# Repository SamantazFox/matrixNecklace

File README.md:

# matrixNecklace

Index
-----

* [Introduction](#introduction)
* [Project's Description](#projects-description)
* [Folders](#folders)
* [Known Issues](#known-issues)
* [To Do](#to-do)

Introduction
------------

This project is a simple customizable necklace, based on an AtTiny2313a (or
alternatively an ATtiny48/88) and a 8x8 dot LED matrix.

The very first idea came from furrtek's mind, called **jewelmatrix**. You can
find his project on [his website](http://furrtek.free.fr/?a=jewelmatrix)
(french).

The idea behind this project was to improve Furrtek's project and add a few
options, such as a rechargeable Li-Ion battery (instead of a coin cell) and a
cross-platform tool to add custom patterns on the fly, without the need to
rebuild and flash the ATtiny every time.

Implemented features :
	* Fully customizable patterns
	* Rechargeable by USB

Planned features :
    * Easy on-the-fly programmation by any device running **\*nix**,
    **windows**, **MacOS** or **android** operating system, using the device's
    screen as the transmission support
    * USB connection to host device (faster than screen transmision)

Project's Description
-------------------

* matrixEditor
    - matrixEditor is the UI for matrixNecklace's patterns creation.
    - Based on the FLTK graphic library.
    - Still at experimental level.

* matrixNecklace
    - One of the following microntrollers:
        * An ATtiny2313/2313a/4313: easy soldering solution
        * An ATtiny48/88: if you feel adventurous to solder QFN32 :P
    - 8x8 dot LED matrix
    - Li-Ion battery, which can be recharged via micro USB type B

Folders
-------

* **/doc**
    - Sphinx documentation
    - Datasheets

* **/editor**
    - C++ Cross-platform editor source code
    - Compile script and instructions

* **/firmware**
    - AVR hardware source code
    - Compile script and instructions
    - Basic patterns (for reference)
    - Arduino sketch used to determine matrixes' pinout

* **/hardware**
    - **/hardware/schematic**
        - KiCad librarties
        - KiCad schematic/pcb files
        - Bill of material

* **/licenses**
    - Project's license file(s)
    - Every libraries used's specific license file(s)

Known Issues
------------

* 50/60 Hz differences may cause problems for screen transmission upload

To Do
-----

* Documentation
    - Sphinx documentation
    - Compiling HowTo

* Editor
    - Patterns import/export
    - Patterns ordering and timings
    - Integrated compiler (and it's output)
    - Device uploader

* Firmware
    - Correct pinout/registers match
    - Update for AtTiny48/88
    - Create custom bootloader
    - Add USB support

* Hardware
    - Finish pinout
    - Finish chips libraries
    - Release schematics
    - Create BOM
    - Still AtTiny2313a version ?
    - Mini USB type B version ?

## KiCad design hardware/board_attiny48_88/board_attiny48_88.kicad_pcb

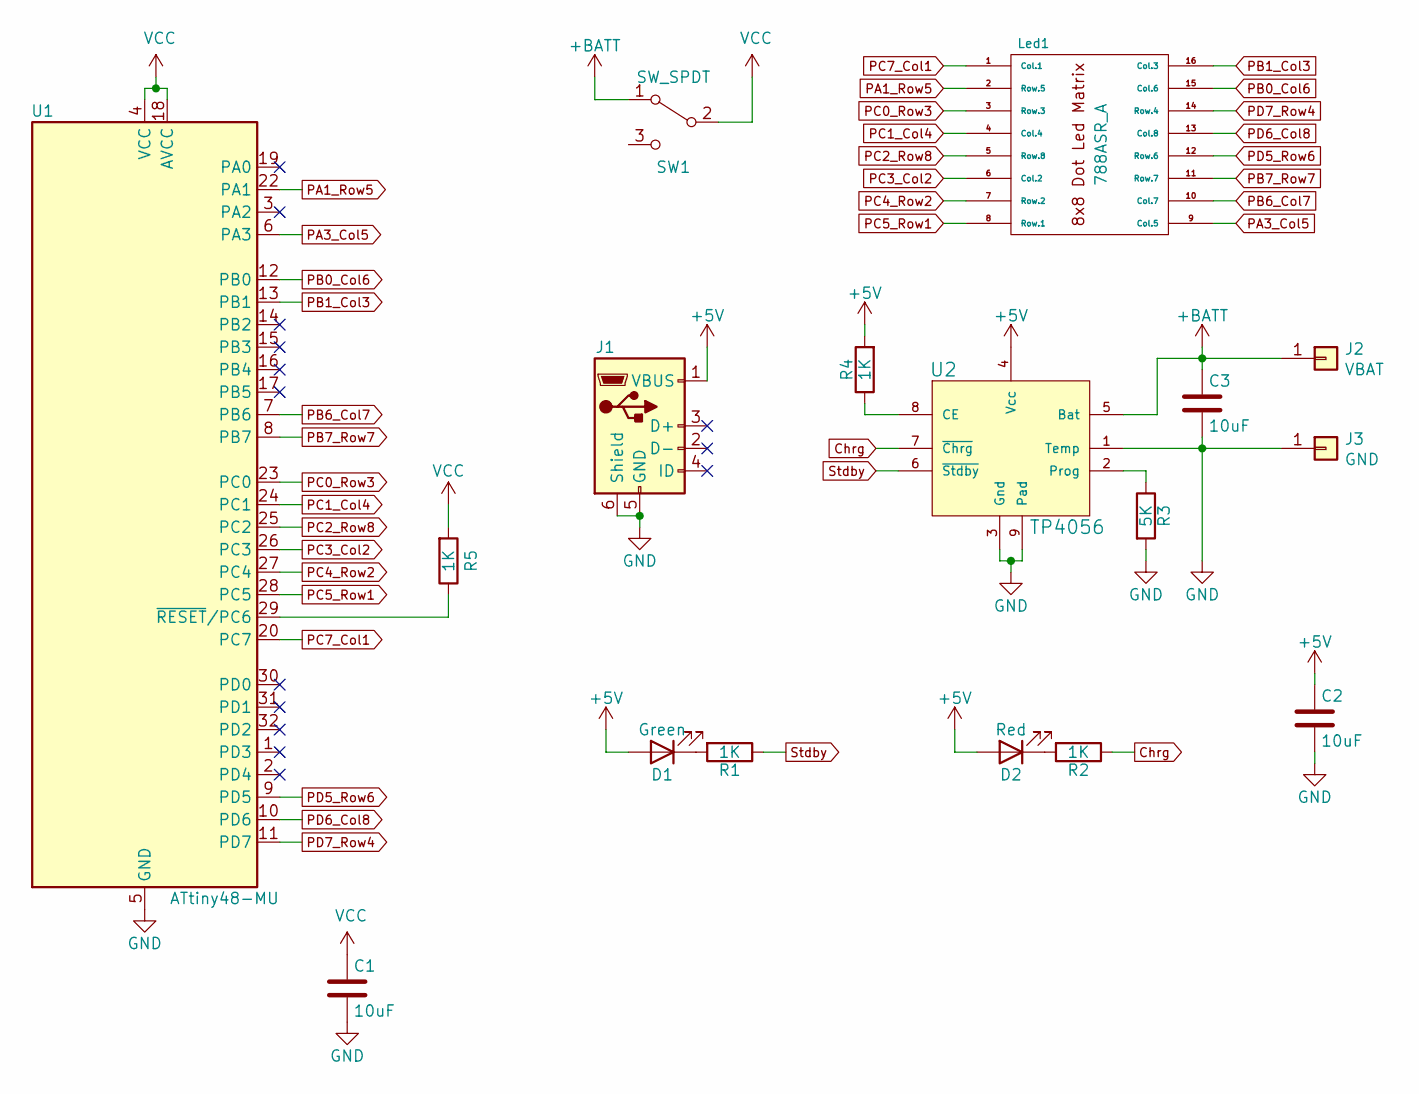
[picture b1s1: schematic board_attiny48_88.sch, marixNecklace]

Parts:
C1, C2, C3: 10uF; C_0603_1608Metric_Pad1.05x0.95mm_HandSolder
D1: Green; LED_0603_1608Metric_Pad1.05x0.95mm_HandSolder
D2: Red; LED_0603_1608Metric_Pad1.05x0.95mm_HandSolder
J1: USB; USB_Micro-B_Molex_47346-0001
J2: VBAT; SolderWirePad_1x01_SMD_1x2mm
J3: GND; SolderWirePad_1x01_SMD_1x2mm
Led1: 788ASR_A; ASR788
R1, R2, R4, R5: 1K; R_0603_1608Metric_Pad1.05x0.95mm_HandSolder
R3: 5K; R_0603_1608Metric_Pad1.05x0.95mm_HandSolder
SW1: SW_SPDT; SW_SPDT_PCM12
U1: ATtiny48-MU; QFN-32-1EP_5x5mm_P0.5mm_EP3.1x3.1mm
U2: TP4056; Diodes_SO-8EP

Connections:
+5V: C2.1, D1.2 (A), D2.2 (A), J1.1 (VBUS), R4.2, U2.4 (Vcc)
+BATT: C3.1, J2.1, SW1.1 (A), U2.5 (Bat)
Chrg: R2.1, U2.7 (~Chrg)
GND: C1.2, C2.2, C3.2, J1.5 (GND), J1.6 (Shield), J3.1, R3.2, U1.5 (GND), U1.21 (GND), U1.33 (GND), U2.1 (Temp), U2.3 (Gnd), U2.9 (Pad)
unnamed: D1.1 (K), R1.2
unnamed: D2.1 (K), R2.2
unnamed: R3.1, U2.2 (Prog)
unnamed: R4.1, U2.8 (CE)
unnamed: R5.1, U1.29 (~RESET~/PC6)
PA1_Row5: Led1.2 (Row.5), U1.22 (PA1)
PA3_Col5: Led1.9 (Col.5), U1.6 (PA3)
PB0_Col6: Led1.15 (Col.6), U1.12 (PB0)
PB1_Col3: Led1.16 (Col.3), U1.13 (PB1)
PB6_Col7: Led1.10 (Col.7), U1.7 (PB6)
PB7_Row7: Led1.11 (Row.7), U1.8 (PB7)
PC0_Row3: Led1.3 (Row.3), U1.23 (PC0)
PC1_Col4: Led1.4 (Col.4), U1.24 (PC1)
PC2_Row8: Led1.5 (Row.8), U1.25 (PC2)
PC3_Col2: Led1.6 (Col.2), U1.26 (PC3)
PC4_Row2: Led1.7 (Row.2), U1.27 (PC4)
PC5_Row1: Led1.8 (Row.1), U1.28 (PC5)
PC7_Col1: Led1.1 (Col.1), U1.20 (PC7)
PD5_Row6: Led1.12 (Row.6), U1.9 (PD5)
PD6_Col8: Led1.13 (Col.8), U1.10 (PD6)
PD7_Row4: Led1.14 (Row.4), U1.11 (PD7)
Stdby: R1.1, U2.6 (~Stdby)
VCC: C1.1, R5.2, SW1.2 (B), U1.4 (VCC), U1.18 (AVCC)

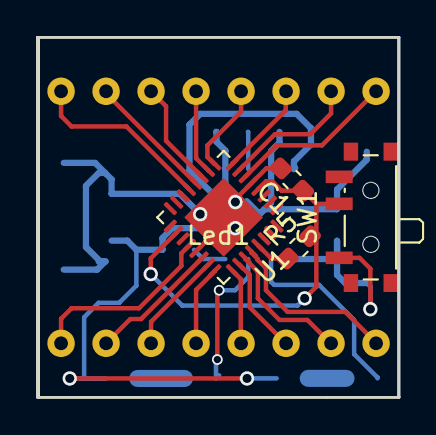
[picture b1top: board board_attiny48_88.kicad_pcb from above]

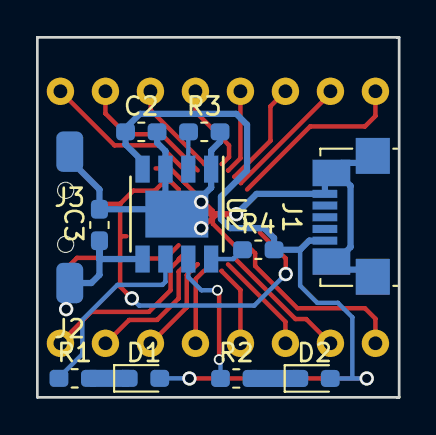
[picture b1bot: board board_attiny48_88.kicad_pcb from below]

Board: 2 copper layers, 20.1 x 20.0 mm, 17 parts (12 on the bottom side), 27 nets.

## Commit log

2017-06-25 Getting back to work on git. Committing many changes.
2017-06-30 Cleaned up patterns.h and removed useless code in blinky.c
2017-06-30 First commit (recreating repo)
2017-06-30 Missing files
2017-06-30 Removed useless code in blinky.c
2017-06-30 Removed test file ^^
2017-07-01 Disappearing file test
2017-07-01 converted `char` and `int` to `uint8_t`
2017-09-14 Added parts datasheet. Filled README.md.
    Edited makefile.
    Removed WIP Blinky.C file.
    Modified patterns formatting.
2017-09-14 Moved code to the firmware/ sub-directory.
2017-09-15 Updated README.md.
2017-09-17 Licenses update
    Changed license from BSD 2-clause to BSD 3-clause.
    Added individual copies for library-specific licenses.
2017-09-17 Moved arduino folder to firmware/
2017-09-18 Cleaned up firmware/Makefile. Added help in firmware/Makefile.
2017-09-23 Switched from short/char to uint8_t
    Removed useless code.
    Improved comments in firmware/Makefile.
2017-12-08 Added matrixEditor part of the project Very basic version, just a matrix of stylized buttons.
2017-12-08 Updated README.md
    Reordered infos and created index
    Complete redo of specifications / added editor specs
    Redone folder list
    Added ToDo list
    Added FLTK license
    Removed Qt licenses
2017-12-09 Fixed README.md broken links
2017-12-24 Matrix restructuration Each line is now a separate group.
2017-12-26 Added a menu bar to the window
2018-01-17 Reformatted ledMatrix architecture Leds are all child of ledMatrix and have a unique ID
    Separated menuEntries code in a separate cpp file
    In order to reduce matrix size, Leds graphics are now 48x48 px
    Also fixed a minor typo on matrixEditor.cpp's last #endif
2018-01-17 Added a text field for info/logs report
2018-01-18 Added formatting to log output
2018-01-23 Logs are now globally available
    Minor typo fixes
    Copyright update
2018-01-23 Moved class "Led" to it's own file
2018-01-28 Get Leds position offste from parent group
2018-01-28 'LedMatrix' and 'Menu' are now two independant classes
    'LedMatrix' creates and positions all its Led children on
    initialization.
    'Menu' class creates the menu and manages callbacks.
    Main window's children are now part of the 'Application' class.
2018-01-28 Change 'Application' class to be an instance of 'Fl_Double_Window'
2018-01-28 'Matrix' method to get all the leds states getData() returns as a uint64_t all the Lesd states, from left to right, and top to bottom.
2018-01-28 Fixed Led index caclculation A small calculation mistake mad the Leds being drawn by columns instead of lines (Led with index 7 ended at the bottom left instead of the top right)
2018-01-28 Fixed the getData() and cd_save() functions
    The matrix element is passed to the getData() function, that means some
    re-ordering of the main header file has to be done in order to solve
    class linking issues :
    - Forward declaration of the project classes
    - Moved project files' #includes to the bottom of the header
    Also removed 'logs' global variable
2018-01-28 Added an icon to the main window
2018-01-29 New style for menu bar and logger field
2018-01-29 Added a new "edit" menu Menu callback functions are not yet implemented
    New method getWindow is meant to be used inside callbacks, to return a
    pointer to the main window from any widget.
2018-01-30 Unified style among objects Removed useless code in 'LoggerField'
2018-01-30 Working data parser Now saving a matrix returns the hex code in the logs field.
2018-02-05 Changed Led::invert method to a write function accepting arguments Needed for future use.
2018-02-05 Added Enums in matrix.h for future use
2018-02-05 Added Matrix::setData and reworked Matrix::getData
    getData now uses 64-bits unsigned integer.
    setData takes also 64-bits unsigned integer.
    Hexadecimal parsing of raw data was moved to a private method of
    'Matrix', so it can be used by getData and setData as a verbose output
    to user.
2018-02-05 Added the callback for the "randomize" menu item.
    Uses the setData function included in the last commit.
2018-02-05 Removed uniform distribution on randomize This is un-needed for 64 bits integers.
2018-02-05 Added "Clear" and "Preferences" intems in "Edit" menu
    Also created the "Clear" callback.
    "Preferences" is reserved for future use.
2018-02-06 Removed useless methods in "LoggerField"
2018-02-06 Removed sizeX and sizeY variables from "Application" class
    Using instead builtin w() and h()
2018-02-06 Fixed minor error in "LoggerField.h"
    Small error folliwing commit 5ed0db79497eafbc726bd6336ff7df08b59738ae
2018-04-01 Moved all dependencies to the beginning of file in matrixEditor.h
2018-04-01 Added a contant to 'Matrix' class for led count All related changes (mainly in "for" loops) were made, too.
    Fixed a missing "this->end()" at the end of Matrix's constructor.
    Added a fallback "return 0;" in Led's event handler.
2018-04-01 Complete rework of the sizing system to include resizeability
    The window size can now be dynamically changed.
    For now, the matrix can't be resized because of buttons' images. So, the
    window is width-restrained.
    Also added a Pos (position) data structure to keep track of the elements
    offset during initialization.
2018-04-01 New struct type and constants for elements' colors
2018-04-08 Complete compiling script rework
    New features :
    - Downloads FLTK source file
    - Program debugging using strace (use `-t`)
    - Avoid running the program after compilation (use `-r`)
    - FLTK is portable (everything belonging to fltk is under
    $fltk_dir/build)
2018-04-08 Quick font fix
    Since my latest install of FLTK library, the program segfaults when
    using any font that is not FL_SCREEN.
    This is a temporary edit, until the problem is solved.
2018-04-08 Use `offset` variable for frame position/size
2018-04-08 Added the frame as a child of `Application`
    Plus some code re-ordering.
2018-04-08 Removed the tile encapsulaion of `LoggerField` as it is useless. The logs field still resizes, as it's part of the `frame` tile.
2018-04-08 Minor typo fix in compile-run
2018-04-09 Minor fix in compile-run
2018-04-10 Added new option to compile-run.sh
    option `-d` enables debugging flags for gcc
    Also made a new flag system, based on makefiles
2018-04-10 Improvements to compile-run script
    - Verbose option (use `-v`)
    - Force rebuild option (make clean) for FLTK library (use `-f`)
    - Compilation flags renamed in order to better match makefile standard
    - Added CONFFLAGS for FLTK's ./configure
2018-04-10 Make use of `-C` flag for make
    instead of changing directory, use `make -C dir/`, which is equivalent
    to `cd dir/ && make`
2018-04-15 Improvements to compile-run.sh
    - Changed behavior of -r (defaults to false)
    - Added help
    - Removed un-needed `cd ..` after documentation compilation
    - Minor improvements to some comments
    - Added a "functions" section, and moved `verbose` there
2018-05-27 Minor changes on README
2018-05-28 Moved #include and #define to header matrixNecklace.h Removed useless bits of code
2018-06-16 matrixEditor first source code release
    Just a very basic version: a matrix of stylized buttons.
2020-11-02 Give repo ownership to Samantaz Fox
2020-11-02 Add KiCad libraries used for this board
2020-11-02 Add board schematics - ATtiny 2313a variant
2020-11-02 Add gitignore
2020-11-05 Add bill of materials (BOM)
2020-11-05 Fix soldermask keepout zones being on the wrong layer
2020-11-06 Add board schematics - ATtiny 48/88 variant
2020-11-06 Add bill of materials (BOM) for ATtiny 48/88 variant
2020-11-06 Add gerbers for ATtiny 2313a variant
2020-11-06 Add gerbers for ATtiny 48/88 variant
2020-11-06 Update gitignore rules
